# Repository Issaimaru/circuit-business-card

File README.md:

# circuit-business-card
NFC対応名刺基板
<br>
<br>
名刺基板です<br>
定番Arduino名刺基板に比べて、実装費が100円未満と安く、部品点数も少ないです<br>
スマホで読み込むとTwitterのリンクなどに飛ばす予定です

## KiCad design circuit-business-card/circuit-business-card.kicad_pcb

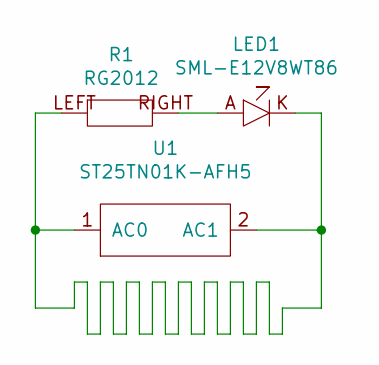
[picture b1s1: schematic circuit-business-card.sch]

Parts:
LED1: SML-E12V8WT86
R1: RG2012
U1: ST25TN01K-AFH5

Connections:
unnamed: LED1.A, R1.RIGHT
unnamed: LED1.K, R1.LEFT, U1.1 (AC0), U1.2 (AC1)

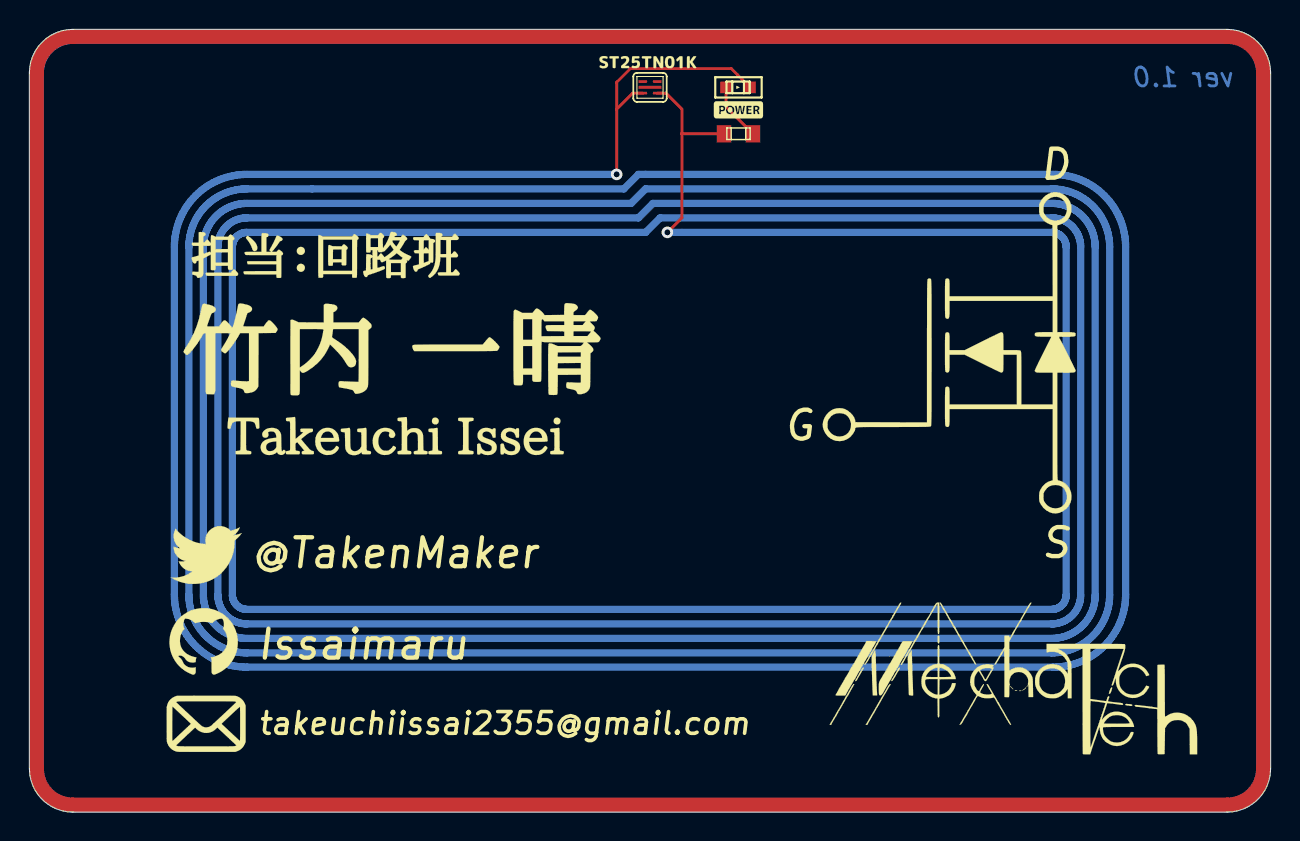
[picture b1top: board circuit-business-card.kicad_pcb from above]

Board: 2 copper layers, 85.6 x 54.0 mm, 3 parts (0 on the bottom side), 2 nets.

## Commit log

2023-01-04 基板完成
2023-01-04 Create LICENCE
